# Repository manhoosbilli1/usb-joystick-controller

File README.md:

# joystick

Compact ATtiny24A-based USB joystick controller

## At a Glance

- **Status**: Partial / WIP
- **Board size**: 33 x 26.5 mm
- **Layers**: 2
- **Components**: 9
- **Key ICs**:
  - U1: ATtiny24A-SS

## Schematic

Full PDF: [reports/schematic.pdf](reports/schematic.pdf)

## Component Roles

- **ATtiny24A-SS** (U1) - 8-bit AVR MCU; runs V-USB-style soft USB or HID-over-UART
- **RKJXV1220001** (SW1) - Alps thumbstick / encoder (rotary + push button)
- **SSSS810701** (S1) - small slide switch (mode / power)

## PCB

**Top copper**

**Bottom copper**

## Bill of Materials

| Refs | Value | Footprint | Qty | MPN | LCSC |
|------|-------|-----------|----:|-----|------|
| C2 | 100nF | PCM_JLCPCB:C_0805 | 1 |  | [C28233](https://www.lcsc.com/product-detail/_C28233.html) |
| R1 | 10kΩ | PCM_JLCPCB:R_0805 | 1 |  | [C17414](https://www.lcsc.com/product-detail/_C17414.html) |
| S1 | SSSS810701 | SSSS810701 | 1 |  |  |
| SW1 | RKJXV1220001 | joystick:SW-TH_RKJXV1220001 | 1 |  |  |
| U1 | ATtiny24A-SS | Package_SO:SOIC-14_3.9x8.7mm_P1.27mm | 1 |  |  |

_3 of 5 line items don't have an LCSC code in the schematic - search [LCSC](https://www.lcsc.com/) or [JLC parts search](https://jlcsearch.tscircuit.com/) by MPN or footprint when sourcing._

## Files

- `joystick.kicad_pro` - KiCad project
- `joystick.kicad_sch` - schematic source
- `joystick.kicad_pcb` - PCB layout source
- `reports/schematic.pdf` - full schematic (printable)
- `reports/bom.csv` - bill of materials
- `reports/pcb-top.svg`, `reports/pcb-bottom.svg` - copper artwork
- `reports/board-stats.json` - KiCad-generated board statistics

---

_Renders and metadata auto-generated by `Backup-KiCadProject.ps1` using KiCad 10.0._

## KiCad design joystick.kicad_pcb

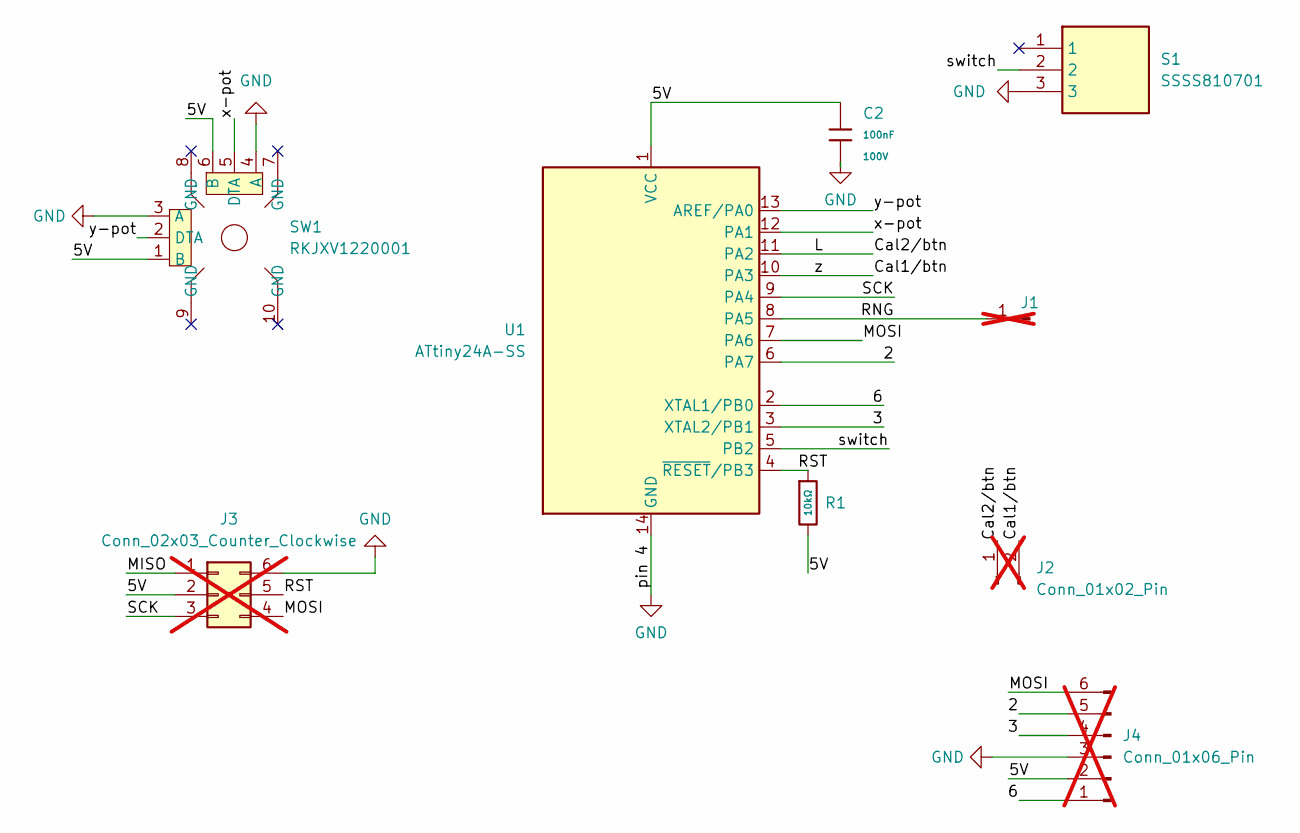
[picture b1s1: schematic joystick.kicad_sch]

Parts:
C2: 100nF; C_0805; Voltage Rated 100V; Tolerance ±10%; Part CL21B104KCFNNNE; LCSC C28233
J1: Conn_01x01_Pin; PinHeader_1x01_P2.54mm_Vertical; not fitted
J2: Conn_01x02_Pin; SolderWire-0.1sqmm_1x02_P3.6mm_D0.4mm_OD1mm; not fitted
J3: Conn_02x03_Counter_Clockwise; PinHeader_2x03_P2.54mm_Vertical; not fitted
J4: Conn_01x06_Pin; JST_ZH_B6B-ZR_1x06_P1.50mm_Vertical; not fitted
R1: 10kΩ; R_0805; Overload Voltage (Max) 150V; Tolerance ±1%; Part 0805W8F1002T5E; LCSC C17414
S1: SSSS810701; Manufacturer_Part_Number SSSS810701; Mouser Part Number 688-SSSS810701
SW1: RKJXV1220001; SW-TH_RKJXV1220001; LCSC Part C219778
U1: ATtiny24A-SS; SOIC-14_3.9x8.7mm_P1.27mm

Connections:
/2: J4.5, U1.6 (PA7)
/3: J4.4, U1.3 (XTAL2/PB1)
/5V: C2.1, J3.2, J4.2, R1.2, SW1.1 (B), SW1.6 (B), U1.1 (VCC)
/6: J4.1, U1.2 (XTAL1/PB0)
/Cal1/btn: J2.2, U1.10 (PA3)
/Cal2/btn: J2.1, U1.11 (PA2)
/MISO: J3.1
/MOSI: J3.4, J4.6, U1.7 (PA6)
/RNG: J1.1, U1.8 (PA5)
/RST: J3.5, R1.1, U1.4 (~RESET/PB3)
/SCK: J3.3, U1.9 (PA4)
/switch: S1.2, U1.5 (PB2)
/x-pot: SW1.5 (DTA), U1.12 (PA1)
/y-pot: SW1.2 (DTA), U1.13 (AREF/PA0)
GND: C2.2, J3.6, J4.3, S1.3, SW1.3 (A), SW1.4 (A), U1.14 (GND)

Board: 2 copper layers, 9 parts (5 on the bottom side), 14 nets, no tracks yet.

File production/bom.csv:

Designator,Footprint,Quantity,Value,LCSC Part #
C2,C_0805,1,100nF,C28233
R1,R_0805,1,10kΩ,C17414
S1,SSSS810701,1,SSSS810701,
SW1,SW-TH_RKJXV1220001,1,RKJXV1220001,C219778
U1,SOIC-14_3.9x8.7mm_P1.27mm,1,ATtiny24A-SS,

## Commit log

2026-05-18 Update backup artifacts
2026-05-18 Enrich README: schematic PNG, component roles, BOM table
